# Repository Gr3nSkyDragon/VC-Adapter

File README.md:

# VC-Adapter

Firmware, PC tools and a PCB for an ESP32-S3 board that carries Nintendo 3DS local wireless (UDS) for Azahar and mGBA-LDN, and
lets a real Game Boy cartridge trade with a 3DS's Virtual Console Pokemon games (Red, Blue, Yellow, Gold, Silver, Crystal).
Firmware 1.8 also carries GB-Link Switch LDN's bridge, for GBA games with a Switch.

## Firmware versions

One codebase, two builds (`firmware/esp32-uds-bridge`, `package-release-bin.ps1 -Profile 1` or `-Profile 2`):

| | Firmware 1.8 (profile 1, `gblink`) | Firmware 1.9 **beta** (profile 2, `vcadapter`) |
| --- | --- | --- |
| Board | Any ESP32-S3 on a PC's or phone's USB | The VC-Adapter board: a XIAO ESP32-S3 on the console's link port (`VC-Adapter-DIY`) |
| 3DS side | Raw radio for Azahar; Virtual Console trades for mGBA, or a real cartridge through a GB-Link and `uds-gblink-relay` | Virtual Console trades for the cartridge on the board's own link port, with no PC (or with `uds-gblink-relay --port` watching) |
| Switch side | GB-Link Switch LDN's bridge, for mGBA's Switch backend, GB-Link's clients or a GB-Link | Not yet: **Game Boy games only** until the board has a GBA side of its own |
| Switching | By what the host speaks, both ways, no power cycle | 3DS side only |
| Image | `esp32-uds-bridge-fw1.8-esp32s3-gblink.bin` | `esp32-uds-bridge-fw1.9-esp32s3-vcadapter.bin` |

Release images and `uds-esp32-setup.exe` (which flashes an image and stores the keys the board needs) are on the Releases page.
See `firmware/esp32-uds-bridge/README.md` for the hardware, flashing, the protocol and what has been verified.

| Folder | What |
| --- | --- |
| `firmware/esp32-uds-bridge` | ESP-IDF firmware for the board; `ldn/` is GB-Link Switch LDN's bridge (see its README) |
| `tools` | PC programs: `uds-esp32-setup.exe` (flash a release image and store the 3DS and Switch keys, no Python or ESP-IDF needed), `uds-gblink-relay.exe` (carries a GB-Link's frames to the board when both are on the PC's USB, or with `--port` shows the log of a VC-Adapter board) |
| `VC-Adapter-DIY` | KiCad 10 project for the VC-Adapter board: **proof of concept, PCB unfinished** (see its README) |

## Building

**Firmware:** ESP-IDF v6.1 at commit `fff9895c82d744c7237be8847347bdd1b07c6643` (GB-Link Switch LDN pins it). In PowerShell:

```
. <ESP-IDF v6.1>\export.ps1
cd firmware/esp32-uds-bridge
.\package-release-bin.ps1               # both images into release/
.\package-release-bin.ps1 -Profile 1    # firmware 1.8 only
.\package-release-bin.ps1 -Profile 2    # firmware 1.9 only
```

**PC tools:** from a Visual Studio x64 developer prompt:

```
cmake -S tools -B build/tools -G Ninja -DCMAKE_BUILD_TYPE=Release
ninja -C build/tools
build\tools\uds-esp32-flash-test.exe
```

## The emulators

Azahar ([azahar_uds](https://github.com/Gr3nSkyDragon/azahar_uds)) and mGBA-LDN ([mgba_LDN](https://github.com/Gr3nSkyDragon/mgba_LDN))
each keep their own copy of the PC side of the USB framing, built into the emulator. The firmware's `main/uds_wire.h` is the
reference for it: a change to the framing changes this repository and both emulators. `firmware/esp32-uds-bridge/test/wire_test.c`
shares golden vectors with Azahar's `src/tests/core/hle/service/nwm/esp32_wire.cpp`.

## Licences

Firmware and PC tools: GPL-3.0-or-later (`LICENSE`). GB-Link Switch LDN's bridge (`firmware/esp32-uds-bridge/ldn`) is
AGPL-3.0, its LDN protocol components GPL-3.0 (their own `LICENSE` and `LDN-GPL-3.0.txt`); firmware 1.8 contains it, so a 1.8
image as a whole is distributed under AGPL-3.0. Firmware 1.9 leaves it out. PCB: MIT (`VC-Adapter-DIY/LICENSE`);
`VC-Adapter-DIY/gba_linkport` is MIT from GB-Link-USB-DIY (its own `LICENSE`). Three files stay MPL-2.0, as their headers say:
`tools/src/md5.c` and `md5.h` (mGBA's, by Jeffrey Pfau) and `tools/src/esp32-serial.c` (mGBA-LDN, with changes by Alex Howe).
The firmware's `main/gbwrap/include/mgba-util` stand-ins describe mGBA's interfaces.

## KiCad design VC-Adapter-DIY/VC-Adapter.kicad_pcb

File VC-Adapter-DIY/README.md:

# VC-Adapter-DIY

**Proof of concept. The PCB is unfinished and has not been fabricated or tested.** The circuit itself has been proven on a
breadboard (see below); the board layout is a work in progress.

A KiCad 10 project for the VC-Adapter: a Seeed XIAO ESP32-S3 plugged straight into a GBA, GBC or Game Boy's link port, with no
GB-Link (Pico) and no PC. It runs firmware **1.9 (beta)**, the VC-Adapter board build of `../firmware/esp32-uds-bridge`, which
clocks the cartridge itself and trades with a 3DS's Virtual Console Pokemon games over the 3DS's local wireless. The Game Boy
side only for now: Gen 3 (GBA) games need the board's own GBA side, which is still to come.

## Circuit

| Part | What |
| --- | --- |
| U1 | Seeed XIAO ESP32-S3 (DIP) |
| U2 | SparkFun BOB-12009 bidirectional level shifter (BSS138; clones work) |
| J1 | GBA link port plug (`gba_linkport/gba_linkport.pretty/GBALinkPort_Male`), going straight into the console |
| R1, R2 | 10 kOhm each: the console sense divider on pin 1 |
| R3, R4, R5, D1 | The chip enable from pin 1: R4 and R5 in series, R3 (1 kOhm) to GND, D1 clamping to 3V3 |

The link port's signals are 5 V when a GBA runs a Game Boy cartridge (3.3 V for a GBA game) and the ESP32's pins take 3.3 V, so
the shifter's high side runs from the port's own VCC (pin 1) and follows the console; its low side runs from the XIAO's 3V3. No
resistors are needed for the link signals. The pinout is the one the firmware expects (`sdkconfig.vcadapter`, the shared VC-Adapter / GB-Link
pinout); SI and SO are the adapter's, as in the GB-Link's notation:

| Plug pin (console's signal) | Shifter | XIAO ESP32-S3 |
| --- | --- | --- |
| 1 (VCC) | HV | - |
| 2 (SO, the console's output) | HV1 / LV1 | D1 = GPIO2, the adapter's SI |
| 3 (SI, the console's input) | HV2 / LV2 | D2 = GPIO3, the adapter's SO |
| 4 (SD) | HV4 / LV4 | D3 = GPIO4 (unused by a Game Boy) |
| 5 (SC, the clock) | HV3 / LV3 | D0 = GPIO1 |
| 6 (GND), plug shield | GND (both sides) | GND |
| - | LV | 3V3 |

A plug that goes into the console has pins 2 and 3 this way round; a socket with a link cable to the console would have them
the other way (the cable crosses SO and SI).

### Console sense and chip enable

Both take the console's pin 1, which is 5 V with a Game Boy game, 3.3 V with a GBA game and 0 V with the console off:

- **Chip enable:** pin 1 through R4 and R5 drives the ESP32's EN, held low by R3 while the console is off and clamped to the
  3V3 rail by D1, so the board only runs while the console is on. The battery stays on the XIAO's BAT pads, where the XIAO's
  own charger keeps it charged from USB-C.
- **Console sense:** R1 and R2 halve pin 1, so the firmware can tell a Game Boy game from a GBA game.

The XIAO's EN and MTCK are pads on its underside, not on its pin headers, so the board brings these two signals out and they are
wired to the pads by hand.

## Status

- Breadboard (XIAO ESP32-S3, BOB-12009, a GBA link plug, wired as above): retail Pokemon Red traded with Virtual Console Blue
  on a 3DS through firmware 1.9, with the board on its own and with a PC watching (`uds-gblink-relay --port`).
- PCB: unfinished, not fabricated. The console sense divider and the chip enable are drawn but not yet built or tested.
- Firmware: does not read the console sense yet. Its sense input (`CONFIG_UDS_LINK_PORT_SENSE_GPIO`, off by default) needs an
  ADC pin (GPIO1 to GPIO10 on the ESP32-S3); MTCK is GPIO39, which can be read only as high or low.

## Licence

MIT (`LICENSE`). `gba_linkport` is MIT from GB-Link-USB-DIY (its own `LICENSE`).

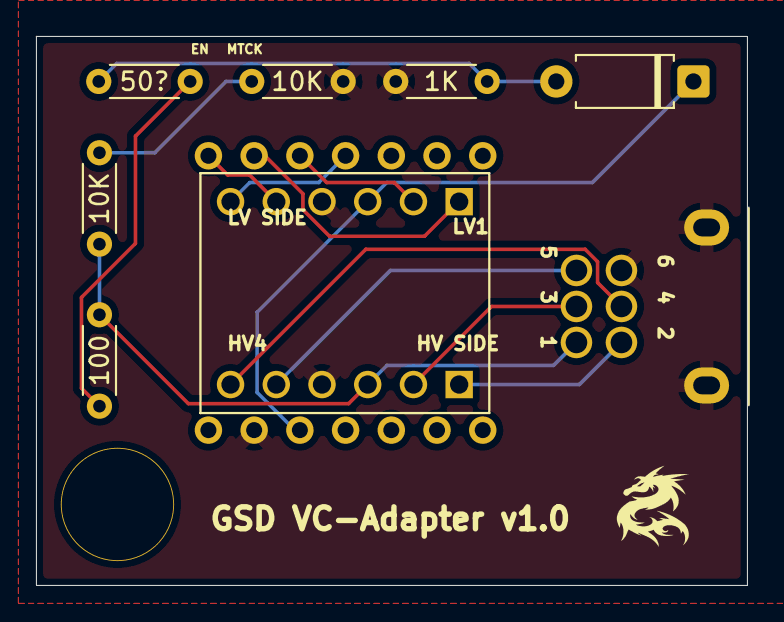
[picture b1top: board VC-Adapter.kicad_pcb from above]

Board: 2 copper layers, 39.5 x 30.5 mm, 9 parts (1 on the bottom side), 14 nets.

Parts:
1K: 1k; R_Axial_DIN0204_L3.6mm_D1.6mm_P5.08mm_Horizontal
10K, 10K#2: 10K; R_Axial_DIN0204_L3.6mm_D1.6mm_P5.08mm_Horizontal
50?: 50?; R_Axial_DIN0204_L3.6mm_D1.6mm_P5.08mm_Horizontal
100: 100; R_Axial_DIN0204_L3.6mm_D1.6mm_P5.08mm_Horizontal
D1: D; D_A-405_P7.62mm_Horizontal
J1: gba_linkport; GBALinkPort_Male
U1: XIAO_ESP32_S3; XIAO-ESP32-S3-DIP
U2: BOB-12009; CONV_BOB-12009

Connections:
GND: 1K.2, 10K.2, J1.6, J1.SH (Pin_7), U1.13 (GND), U2.GND_1 (GND), U2.GND_2 (GND)
unnamed: 1K.1, 50?.2, D1.2 (A)
unnamed: D1.1 (K), U1.12 (3V3), U2.LV
unnamed: 10K#2.1, 100.1, J1.1, U2.HV
unnamed: J1.2, U2.HV1
unnamed: J1.3, U2.HV2
unnamed: J1.4, U2.HV4
unnamed: J1.5, U2.HV3
unnamed: 10K.1, 10K#2.2
unnamed: 50?.1, 100.2
unnamed: U1.1 (D0/GPIO1), U2.LV3
unnamed: U1.2 (D1/GPIO2), U2.LV1
unnamed: U1.3 (D2/GPIO3), U2.LV2
unnamed: U1.4 (D3/GPIO4), U2.LV4
